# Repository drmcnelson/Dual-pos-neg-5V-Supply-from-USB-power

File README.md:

# Dual-pos-neg-5V-Supply-from-USB-power
Provides +/-5 power from USB power, KiCAD design files.

## Introduction
This repository provides KiCAD files for a filtered +/-5V supply that I use with some of the precision instrumentation circuits that I build and use in my lab.  These are often operated by microcontrollers such as Arduino and Teensy that typically provide only +5V (USB) or 3.3V power.
While a lot can be done in designing for single ended supplies, there are some important instrumention circuits that inherently require a dual supply.

In this design, the +5V supply is based on an LT1930 configured as a SEPIC converter to accomodate 
supply voltages that may be greater or lesser than the 5V output.
The -5V suppy is based on an LT1931, an inverting DC/DC converter.
The datasheets describe the supplies as providing 350mA and 300mA, respectfully.
In this design, the circuits are connected by jumpers to the input power connector.
Either supply can be turned off individually by removing the corresponding jumper which is located next to the 5V input.

<br>
## Obtaining board

The board can be ordered, assembled, at

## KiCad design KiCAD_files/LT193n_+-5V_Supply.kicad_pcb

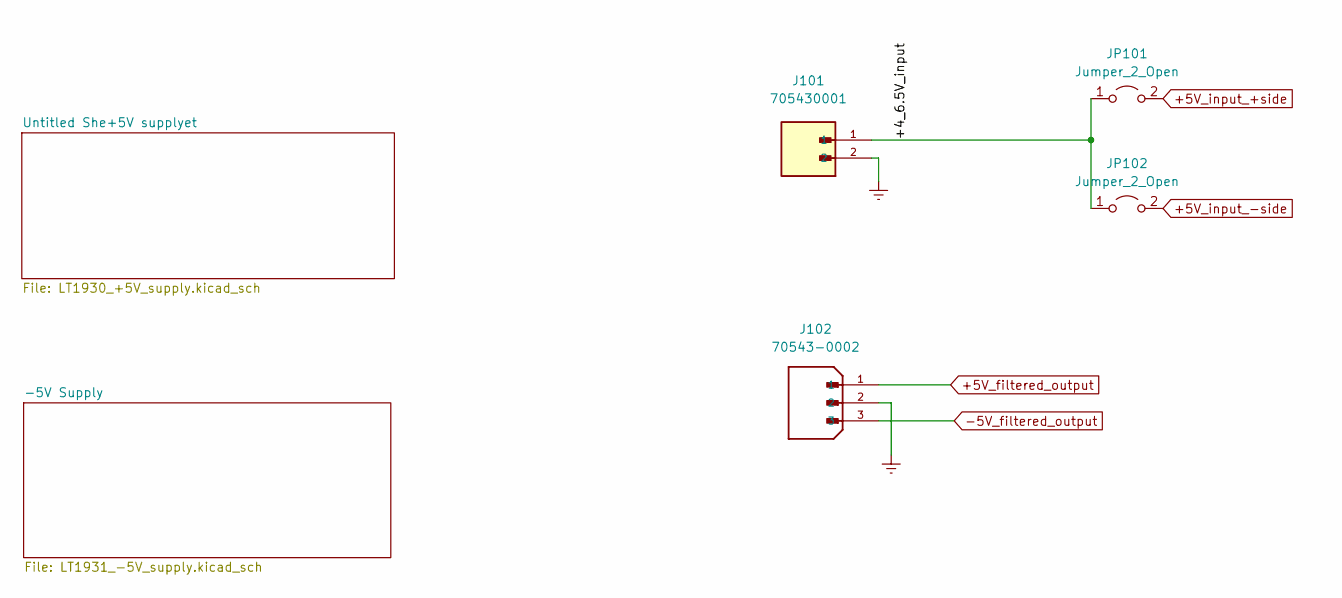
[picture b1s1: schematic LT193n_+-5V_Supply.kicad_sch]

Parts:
J101: 705430001; MOLEX_705430001; PARTREV M1; Digikey WM4800-ND
J102: 70543-0002; MOLEX_70543-0002; PARTREV M1; Digikey WM4801-ND
JP101, JP102: Jumper_2_Open; PinHeader_1x02_P2.54mm_Vertical; Digikey 3M156268-02-ND

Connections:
+5V_filtered_output: J102.1; also elsewhere on the board
+5V_input_+side: JP101.2 (B); also elsewhere on the board
+5V_input_-side: JP102.2 (B); also elsewhere on the board
-5V_filtered_output: J102.3; also elsewhere on the board
/+4_6.5V_input: J101.1, JP101.1 (A), JP102.1 (A)
Earth: J101.2, J102.2; also elsewhere on the board

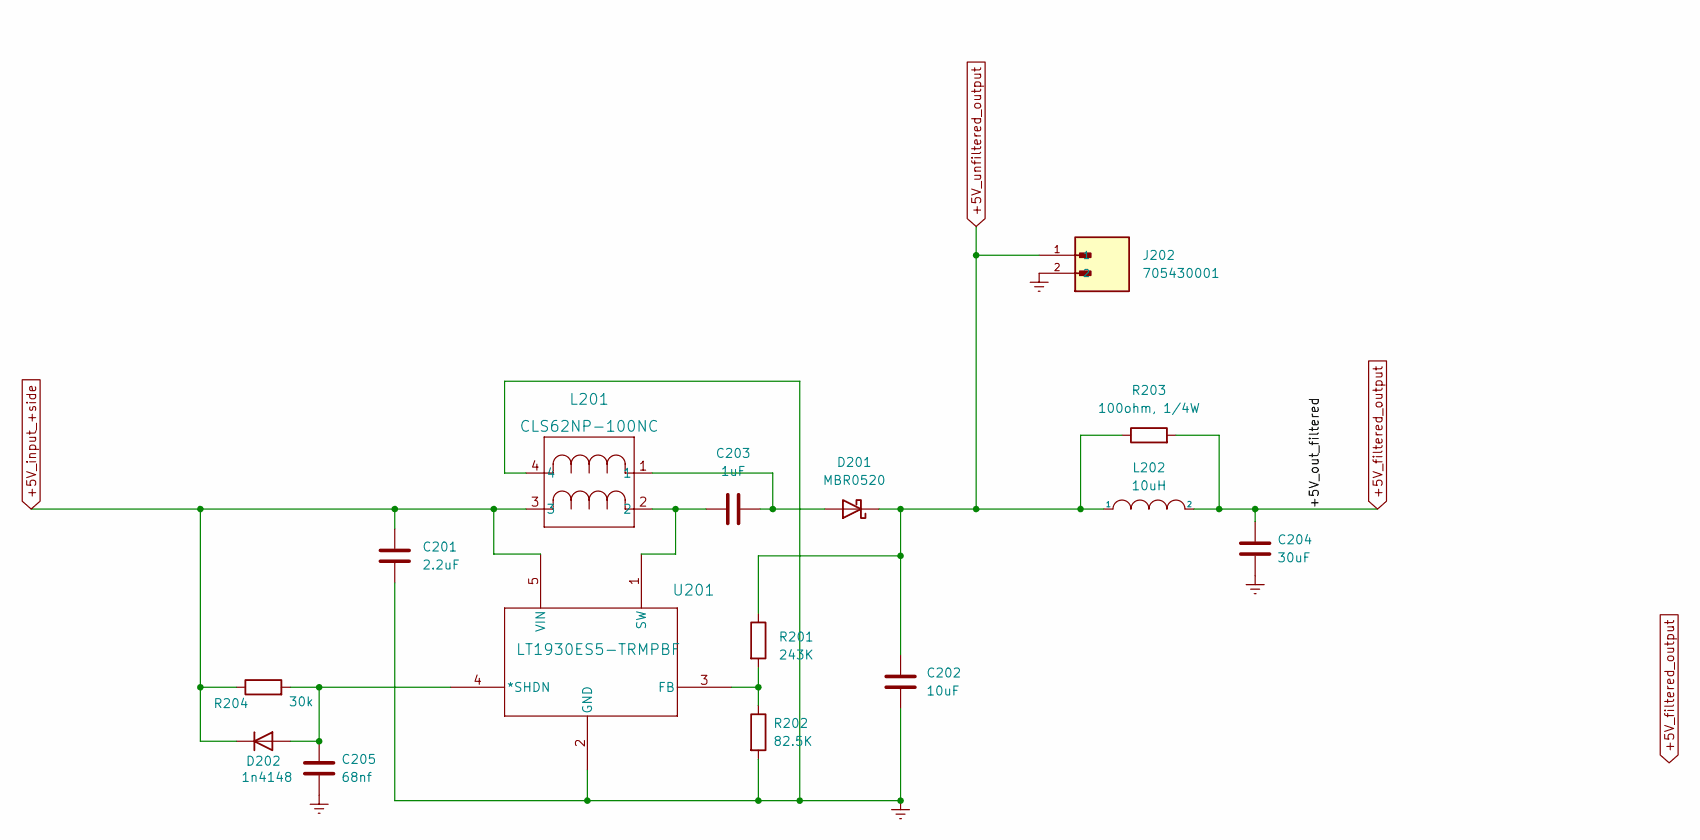
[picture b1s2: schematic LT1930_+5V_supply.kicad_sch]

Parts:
C201: 2.2uF; C_0805_2012Metric; Digikey 587-5919-1-ND
C202: 10uF; C_0805_2012Metric; Digikey 445-5984-1-ND
C203: 1uF; C_0805_2012Metric; Digikey 445-7547-1-ND
C204: 30uF; C_1206_3216Metric; Digikey 445-8046-1-ND
C205: 68nf; C_0805_2012Metric; Digikey 399-C0805C683K5RECAUTO7210CT-ND
D201: MBR0520; D_SOD-123; Digikey 3191-MBR0520CT-ND
D202: 1n4148; D_SOD-323; Digikey 1N4148WS-HE3-08GICT-ND
J202: 705430001; MOLEX_705430001; PARTREV M1; Digikey WM4800-ND
L201: CLS62NP-100NC; CLS62_SUM; Digikey 308-2327-1-ND
L202: 10uH; L_Taiyo-Yuden_NR-40xx; Digikey 587-2886-1-ND
R201: 243K; R_0805_2012Metric; Digikey RMCF0805FT243KCT-ND
R202: 82.5K; R_0805_2012Metric; Digikey RMCF0805FT82K5CT-ND
R203: 100ohm, 1/4W; R_0805_2012Metric; Digikey P16057CT-ND
R204: 30k; R_0805_2012Metric; Digikey 311-30.0KCRCT-ND
U201: LT1930ES5-TRMPBF; TSOT-23-5; Digikey 505-LT1930ES5#TRMPBFCT-ND

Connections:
+5V_filtered_output: C204.1, L202.2, R203.2; also elsewhere on the board
+5V_input_+side: C201.1, D202.1 (K), L201.3, R204.1, U201.5 (VIN); also elsewhere on the board
+5V_unfiltered_output: C202.1, D201.1 (K), J202.1, L202.1, R201.1, R203.1
Earth: C201.2, C202.2, C204.2, C205.2, J202.2, L201.4, R202.2, U201.2 (GND); also elsewhere on the board
unnamed: C203.1, L201.2, U201.1 (SW)
unnamed: C203.2, D201.2 (A), L201.1
unnamed: C205.1, D202.2 (A), R204.2, U201.4 (*SHDN)
unnamed: R201.2, R202.1, U201.3 (FB)

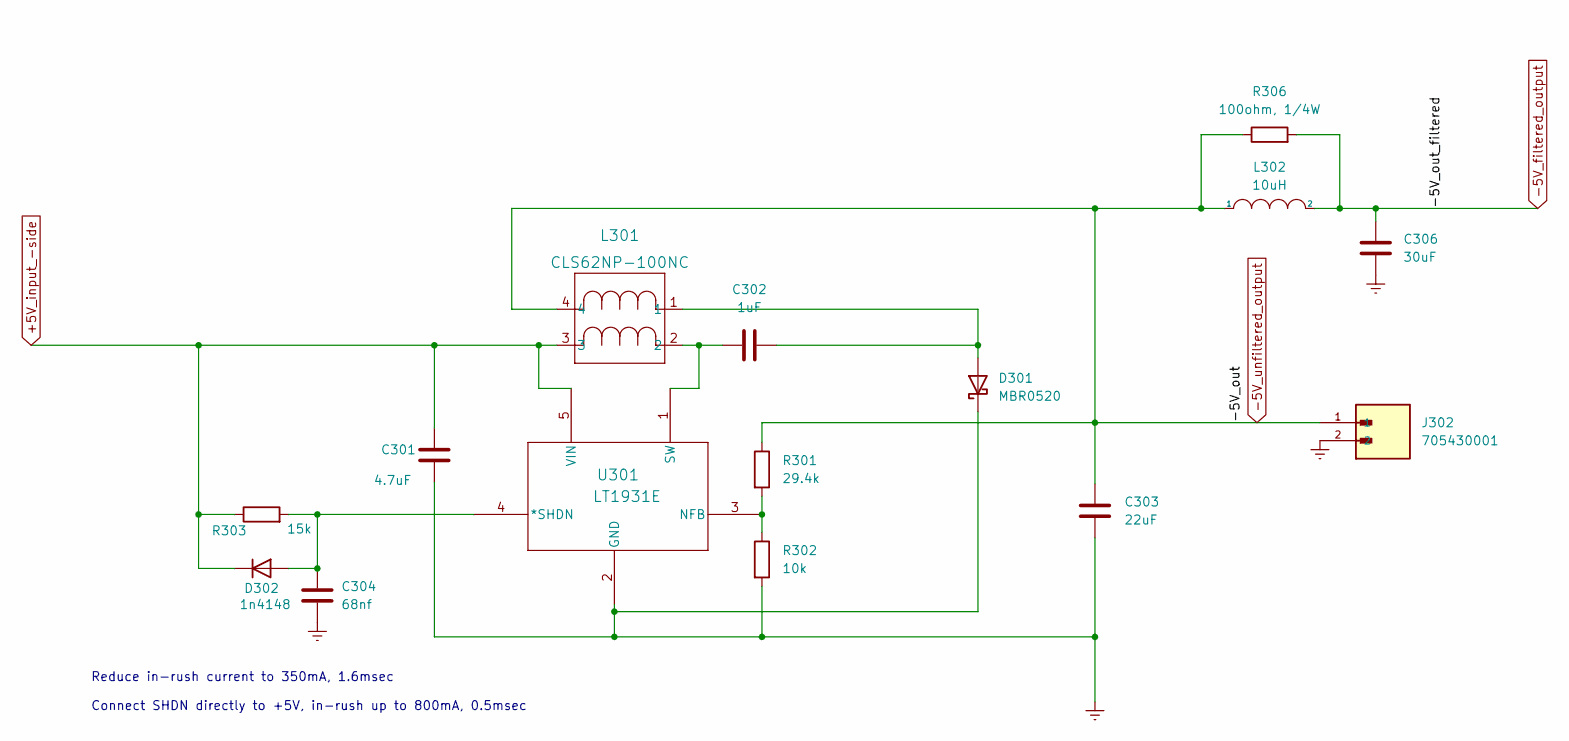
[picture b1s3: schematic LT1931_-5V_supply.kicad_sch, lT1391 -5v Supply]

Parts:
C301: 4.7uF; C_0805_2012Metric; Digikey 490-14532-1-ND
C302: 1uF; C_0805_2012Metric; Digikey 445-7547-1-ND
C303: 22uF; C_0805_2012Metric; Digikey 445-14428-1-ND
C304: 68nf; C_0805_2012Metric; Digikey 399-C0805C683K5RECAUTO7210CT-ND
C306: 30uF; C_1206_3216Metric; Digikey 445-8046-1-ND
D301: MBR0520; D_SOD-123; Digikey 3191-MBR0520CT-ND
D302: 1n4148; D_SOD-323; Digikey 1N4148WS-HE3-08GICT-ND
J302: 705430001; MOLEX_705430001; PARTREV M1; Digikey WM4800-ND
L301: CLS62NP-100NC; CLS62_SUM; Digikey 308-2327-1-ND
L302: 10uH; L_Taiyo-Yuden_NR-40xx; Digikey 587-2886-1-ND
R301: 29.4k; R_0805_2012Metric; Digikey 311-29.4KCRCT-ND
R302: 10k; R_0805_2012Metric; Digikey 311-10.0KCRCT-ND
R303: 15k; R_0805_2012Metric; Digikey 311-15.0KCRCT-ND
R306: 100ohm, 1/4W; R_0805_2012Metric; Digikey P16057CT-ND
U301: LT1931E; TSOT-23-5; Digikey 505-LT1931ES5#TRPBFCT-ND

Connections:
+5V_input_-side: C301.1, D302.1 (K), L301.3, R303.1, U301.5 (VIN); also elsewhere on the board
-5V_filtered_output: C306.1, L302.2, R306.2; also elsewhere on the board
-5V_unfiltered_output: C303.1, J302.1, L301.4, L302.1, R301.1, R306.1
Earth: C301.2, C303.2, C304.2, C306.2, D301.1 (K), J302.2, R302.2, U301.2 (GND); also elsewhere on the board
unnamed: C302.1, L301.2, U301.1 (SW)
unnamed: C302.2, D301.2 (A), L301.1
unnamed: C304.1, D302.2 (A), R303.2, U301.4 (*SHDN)
unnamed: R301.2, R302.1, U301.3 (NFB)

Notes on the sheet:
Reduce in-rush current to 350mA, 1.6msec Connect SHDN directly to +5V, in-rush up to 800mA, 0.5msec

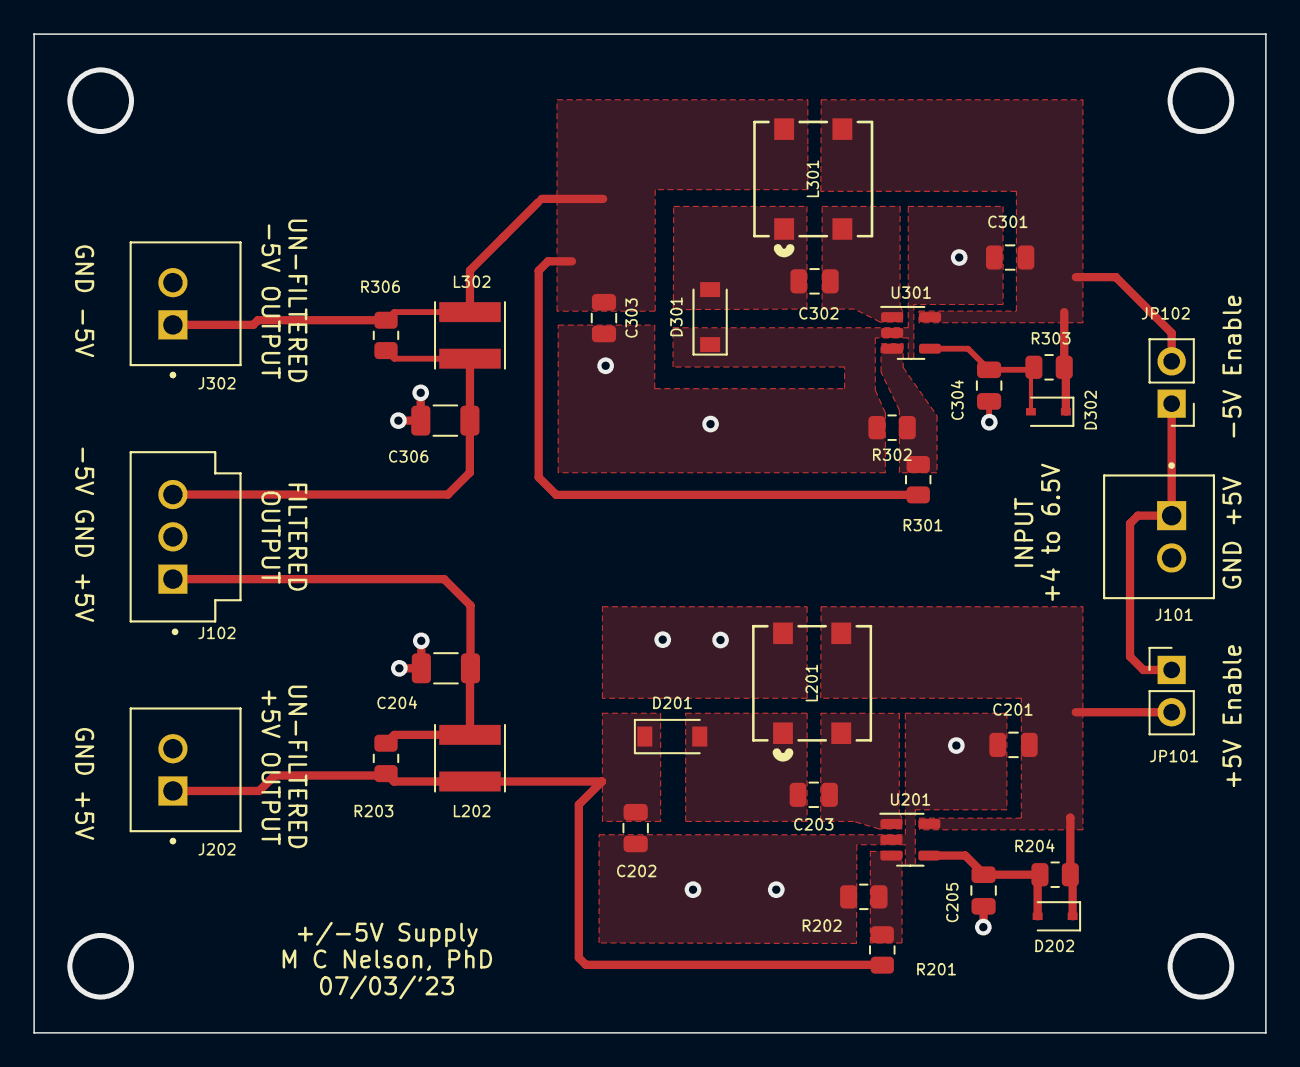
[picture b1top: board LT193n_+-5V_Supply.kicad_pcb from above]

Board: 2 copper layers, 74.0 x 60.0 mm, 34 parts (0 on the bottom side), 16 nets.
